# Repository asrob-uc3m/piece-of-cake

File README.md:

# PIECE-OF-CAKE
Robot siguelíneas de RoboFactory

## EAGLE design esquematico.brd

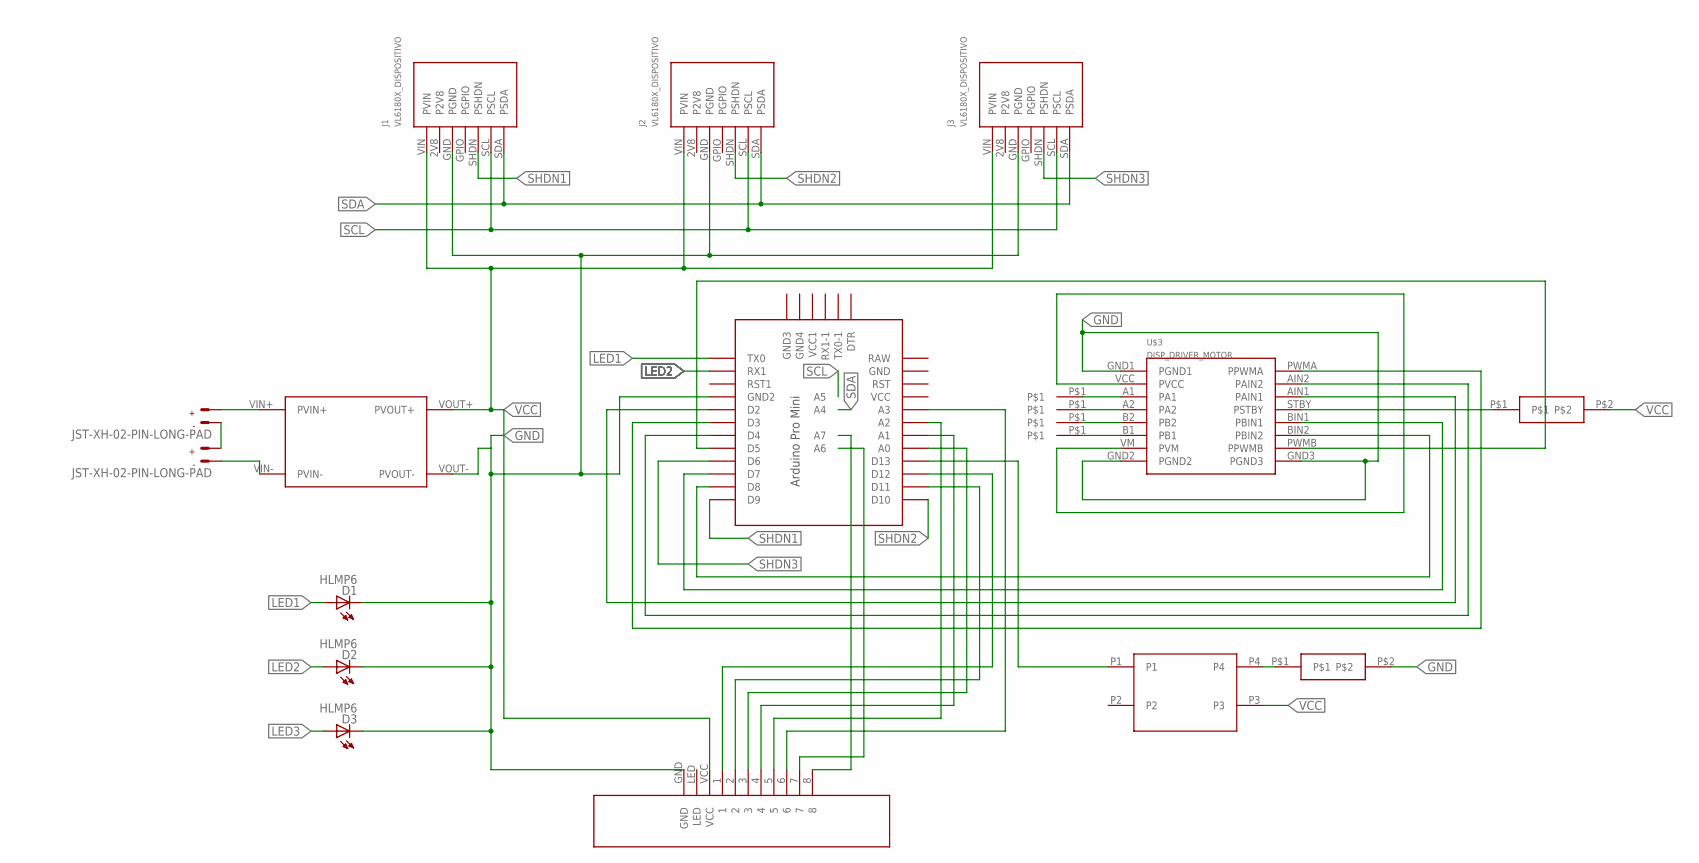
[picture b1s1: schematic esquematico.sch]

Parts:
D1, D2, D3: HLMP6
DC1+: PION_DVC; PIN_PKG
J1, J2, J3: VL6180X_DISPOSITIVO; VL6180X_PKG
U$1: PRO-MINI-2
U$2: R_BUENO_DIPS; R_BUENO_PKG
U$3: DISP_DRIVER_MOTOR; DRIVER_MOTOR
U$4: SENSORLINEA_DISP; SENSORLINEA_PKG
U$5, U$10: RES_DISP; RES_PKG
U$6, U$7, U$8: PION_DVC; PIN_PKG
U$9: BOTON_DEVICE; BOTON_PACK
X1, X2: JST-XH-02-PIN-LONG-PAD; JST-XH-02-PACKAGE-LONG-PAD

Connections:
GND: D1.K, D2.K, D3.K, J1.GND, J2.GND, J3.GND, U$1.GND1 (GND2), U$2.VOUT-, U$3.GND1, U$3.GND2, U$3.GND3, U$4.GND, U$10.P$2
LED1: D1.A, U$1.TX0
LED2: D2.A, U$1.RX1
LED3: D3.A, U$1.D13, U$9.P1
unnamed: U$2.VIN+, X1.2
unnamed: X1.1, X2.2
unnamed: U$2.VIN-, X2.1
unnamed: DC1+.P$1, U$3.A1
unnamed: U$3.A2, U$6.P$1
unnamed: U$3.B2, U$7.P$1
unnamed: U$3.B1, U$8.P$1
unnamed: U$3.STBY, U$5.P$1
unnamed: U$1.D3, U$3.PWMA
unnamed: U$1.D4, U$3.AIN2
unnamed: U$1.D2, U$3.AIN1
unnamed: U$1.D7, U$3.BIN1
unnamed: U$1.D8, U$3.BIN2
unnamed: U$1.D5, U$3.PWMB
unnamed: U$1.D12, U$4.1
unnamed: U$1.D11, U$4.2
unnamed: U$1.A0, U$4.3
unnamed: U$1.A1, U$4.4
unnamed: U$1.A2, U$4.5
unnamed: U$1.A3, U$4.6
unnamed: U$1.A6, U$4.7
unnamed: U$1.A7, U$4.8
unnamed: U$9.P4, U$10.P$1
SCL: J1.SCL, J2.SCL, J3.SCL, U$1.A5
SDA: J1.SDA, J2.SDA, J3.SDA, U$1.A4
SHDN1: J1.SHDN, U$1.D9
SHDN2: J2.SHDN, U$1.D10
SHDN3: J3.SHDN, U$1.D6
VCC: J1.VIN, J2.VIN, J3.VIN, U$2.VOUT+, U$3.VCC, U$3.VM, U$4.VCC, U$5.P$2, U$9.P3

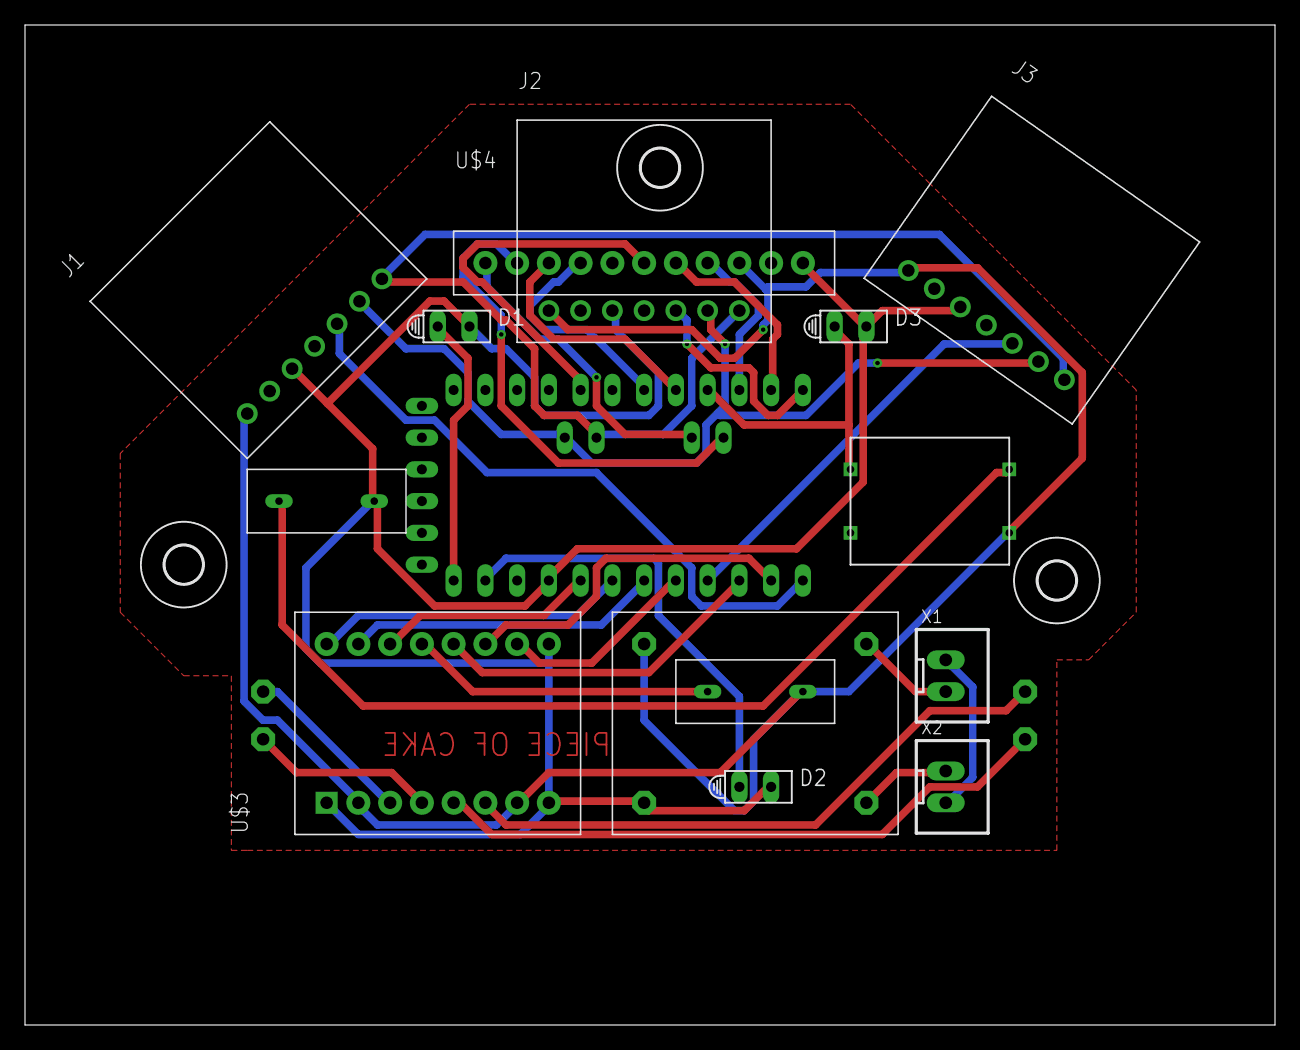
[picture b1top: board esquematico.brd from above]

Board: 2 copper layers, 100.0 x 80.0 mm, 22 parts (0 on the bottom side), 33 nets.

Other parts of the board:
U$11, U$12, U$13: 3,0

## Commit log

2017-12-05 Codigo siguelineas
2017-12-06 Update Codigo siguelineas
2018-05-10 Add files via upload
    PCB gerber
2018-06-25 PCB files
